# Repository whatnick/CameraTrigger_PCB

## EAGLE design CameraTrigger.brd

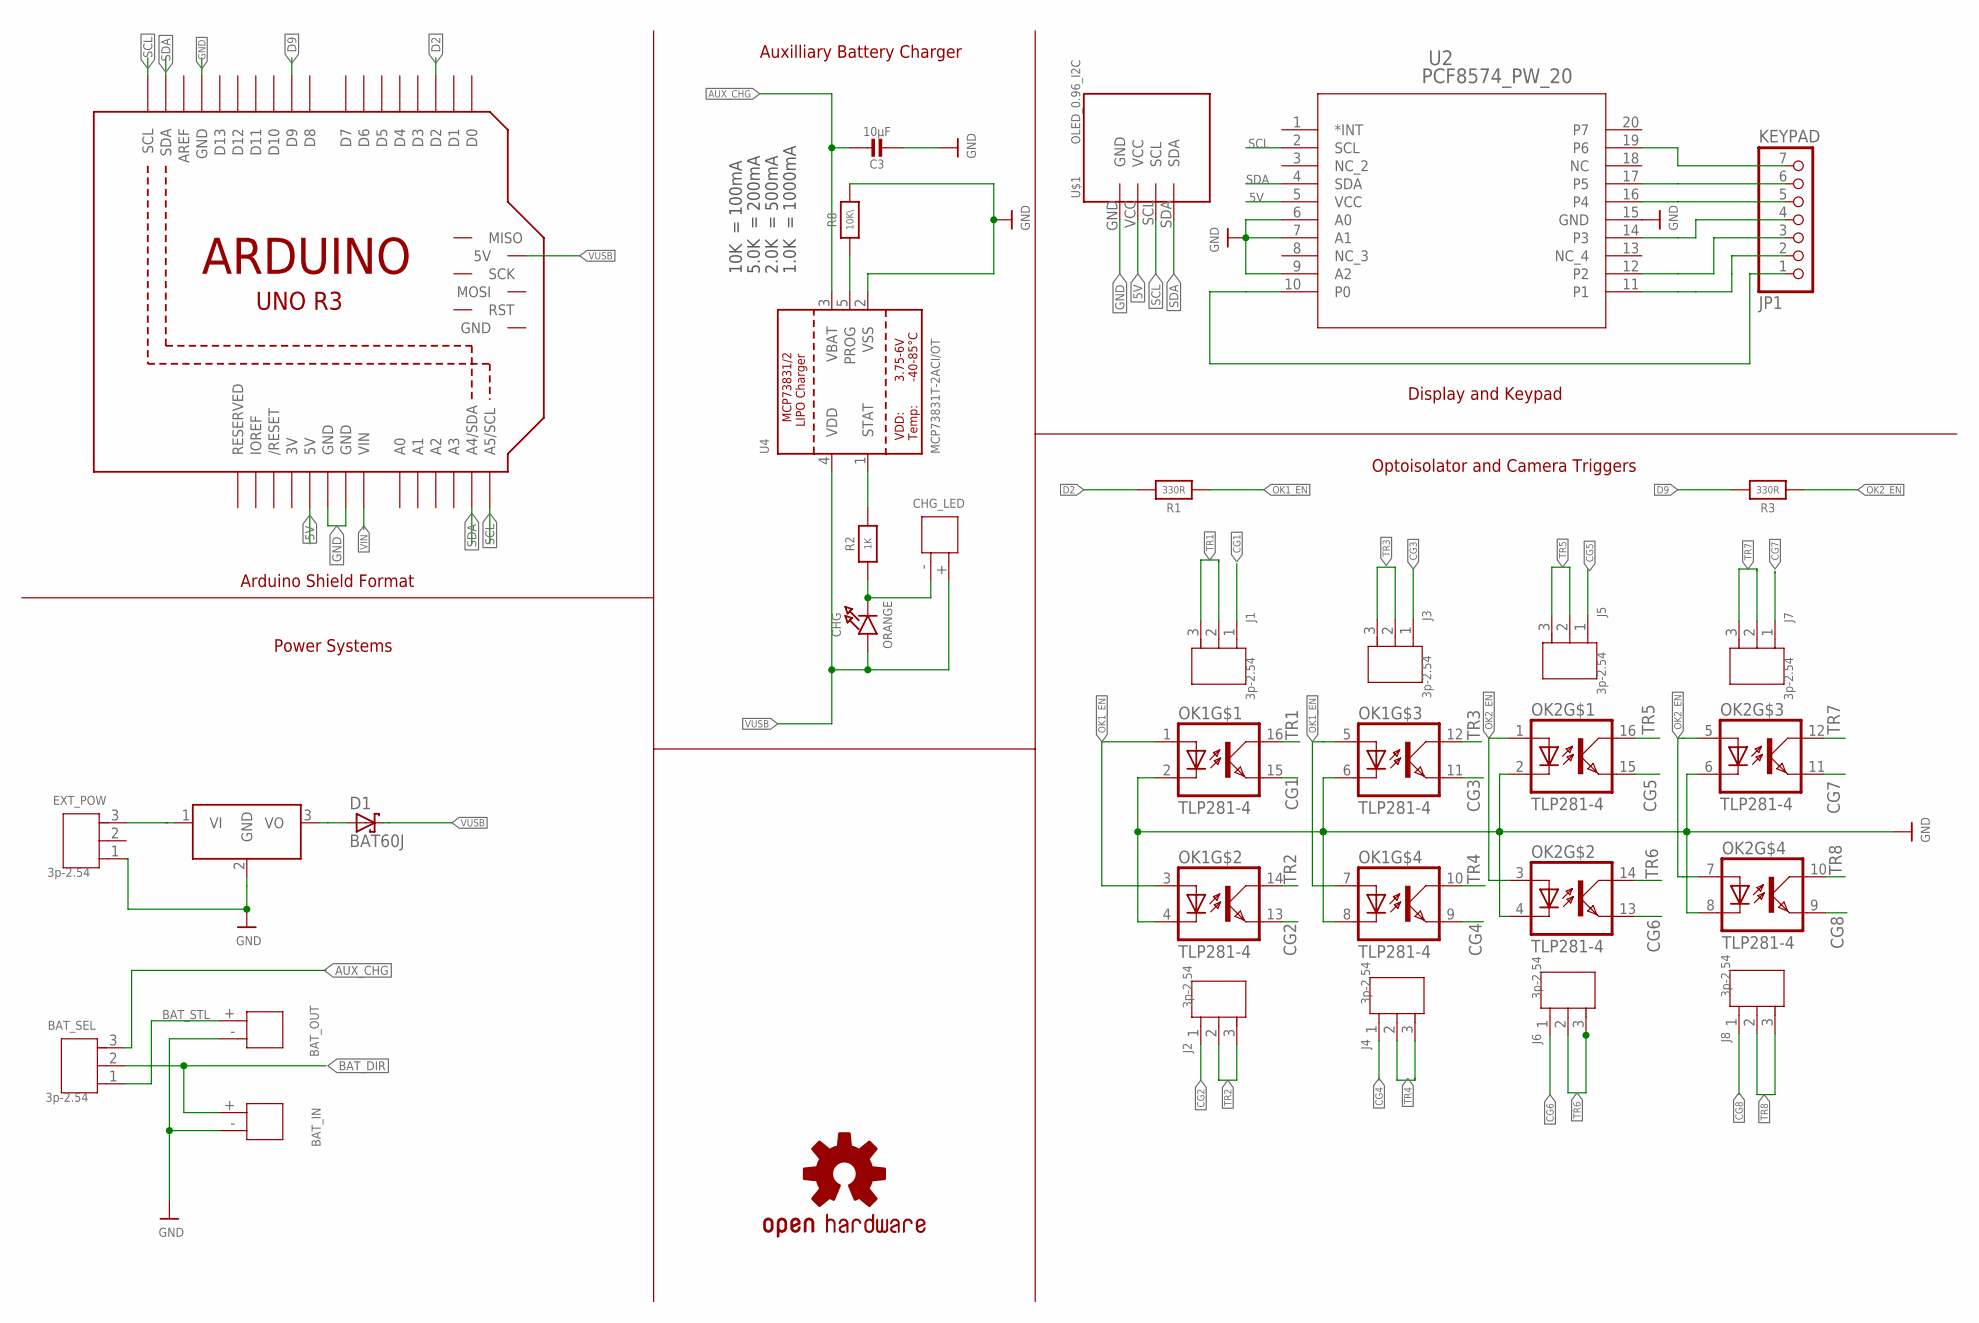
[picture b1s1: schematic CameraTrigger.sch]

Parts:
BAT_IN: 2p-2.0; H2-2.0-6X4.5MM
BAT_OUT: 2p-2.0; H2-2.0-6X4.5MM
BAT_SEL: 3p-2.54; HW3-2.54-7.62X6.6MM
C3: 10µF; 0805-NO
CHG: ORANGE; CHIPLED_0805_NOOUTLINE
CHG_LED: 2p-2.0; H2-2.0-6X4.5MM
D1: BAT60J; SOD323_ST
EXT_POW: 3p-2.54; HW3-2.54-7.62X6.6MM
J1, J2, J3, J4, J5, J6, J7, J8: 3p-2.54; HW3-2.54-7.62X6.6MM
JP1: KEYPAD; 1X07
LOGO1: OSHW-LOGOM; OSHW-LOGO-M
M1: ARDUINO_R3_ICSP; ARDUINOR3_ICSP
OK1, OK2: TLP281-4; MINI-FLAT-16
OKI-78SR-5: DCDC_OKI-78SR; OKI-78SRH
R1, R3: 330R; 0603-NO
R2: 1K; 0603-NO
R8: 10K\; 0603-NO
U2: PCF8574_PW_20; PW20
U4: MCP73831T-2ACI/OT; SOT23-5
U$1: OLED_0.96_I2C

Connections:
3V: M1.3V
5V: M1.5V, U2.5 (VCC), U$1.VCC
AUX_CHG: BAT_SEL.3, C3.1, U4.3 (VBAT)
BAT_DIR: BAT_IN.+, BAT_SEL.2
BAT_STL: BAT_OUT.+, BAT_SEL.1
CG1: J1.1, OK1.15 (EMIT)
CG2: J2.1, OK1.13 (EMIT)
CG3: J3.1, OK1.11 (EMIT)
CG4: J4.1, OK1.9 (EMIT)
CG5: J5.1, OK2.15 (EMIT)
CG6: J6.1, OK2.13 (EMIT)
CG7: J7.1, OK2.11 (EMIT)
CG8: J8.1, OK2.9 (EMIT)
D2: M1.D2, R1.2
D9: M1.D9, R3.2
GND: BAT_IN.-, BAT_OUT.-, C3.2, EXT_POW.1, M1.GND, M1.GND@1 (GND), M1.GND@3 (GND), OK1.2 (C), OK1.4 (C), OK1.6 (C), OK1.8 (C), OK2.2 (C), OK2.4 (C), OK2.6 (C), OK2.8 (C), OKI-78SR-5.2 (GND), R8.2, U2.6 (A0), U2.7 (A1), U2.9 (A2), U2.15 (GND), U4.2 (VSS), U$1.GND
K1: JP1.1, U2.10 (P0)
K2: JP1.2, U2.11 (P1)
unnamed: CHG.C, CHG_LED.-, R2.1
unnamed: D1.A, OKI-78SR-5.3 (VO)
unnamed: R2.2, U4.1 (STAT)
unnamed: R8.1, U4.5 (PROG)
unnamed: JP1.7, U2.19 (P6)
unnamed: JP1.6, U2.17 (P5)
unnamed: JP1.5, U2.16 (P4)
unnamed: JP1.4, U2.14 (P3)
unnamed: JP1.3, U2.12 (P2)
OK1_EN: OK1.1 (A), OK1.3 (A), OK1.5 (A), OK1.7 (A), R1.1
OK2_EN: OK2.1 (A), OK2.3 (A), OK2.5 (A), OK2.7 (A), R3.1
SCL: M1.A5 (A5/SCL), M1.SCL, U2.2 (SCL), U$1.SCL
SDA: M1.A4 (A4/SDA), M1.SDA, U2.4 (SDA), U$1.SDA
TR1: J1.2, J1.3, OK1.16 (COL)
TR2: J2.2, J2.3, OK1.14 (COL)
TR3: J3.2, J3.3, OK1.12 (COL)
TR4: J4.2, J4.3, OK1.10 (COL)
TR5: J5.2, J5.3, OK2.16 (COL)
TR6: J6.2, J6.3, OK2.14 (COL)
TR7: J7.2, J7.3, OK2.12 (COL)
TR8: J8.2, J8.3, OK2.10 (COL)
VEXT: EXT_POW.3, OKI-78SR-5.1 (VI)
VIN: M1.VIN
VUSB: CHG.A, CHG_LED.+, D1.C, M1.5V_ICSP (5V), U4.4 (VDD)

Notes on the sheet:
Display and Keypad
Optoisolator and Camera Triggers
Arduino Shield Format
Power Systems
10K = 100mA
5.0K = 200mA
2.0K = 500mA
1.0K = 1000mA
Auxilliary Battery Charger

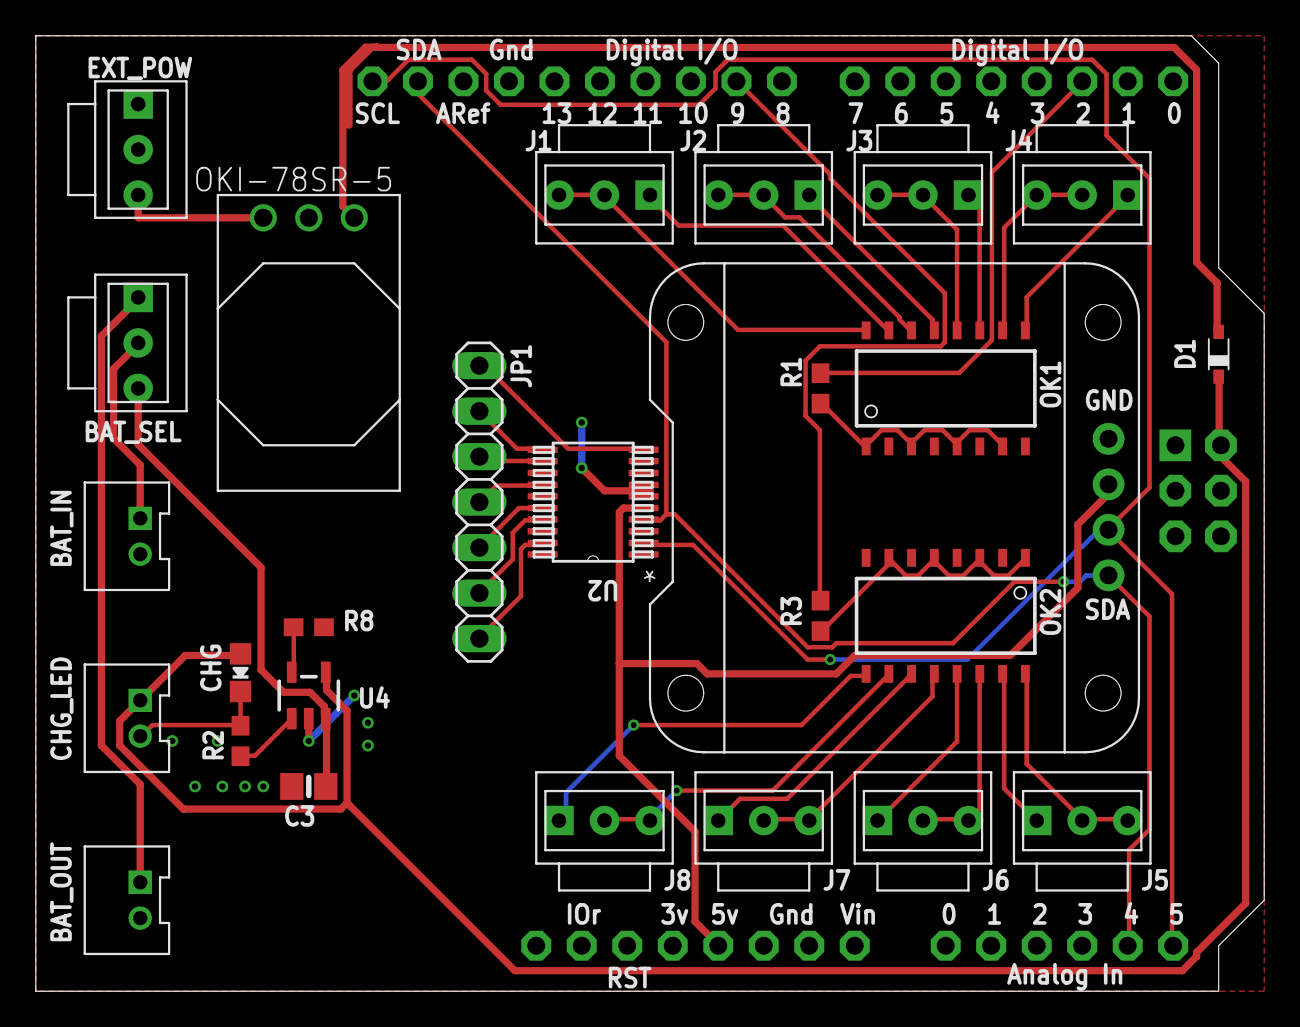
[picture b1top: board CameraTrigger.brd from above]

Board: 2 copper layers, 68.6 x 53.3 mm, 29 parts (1 on the bottom side), 40 nets.

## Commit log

2016-12-15 Intial import of 8 camera triggerboard
2017-01-11 Replace voltage regulator with DC-DC switchmode

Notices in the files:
CameraTrigger.brd:
OSHW Licence: TAPR
parts and their libraries:
SparkFun-Aesthetics: Licensing: Creative Commons ShareAlike 4.0 International - https://creativecommons.org/licenses/by-sa/4.0
microbuilder: This work is placed in the public domain, and may be freely used for commercial and non-commercial work with the following conditions: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
